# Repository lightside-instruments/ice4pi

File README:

hat4pi is an open hardware template for
development Raspberry Pi Hats published by Lightside Instruments AS.

The initial release hat4pi-1.0 includes schematic and PCB
design files for KiCAD.

The project is published by Lightside Instruments AS
under TAPR Open Hardware License. Read the LICENSE file
for details.

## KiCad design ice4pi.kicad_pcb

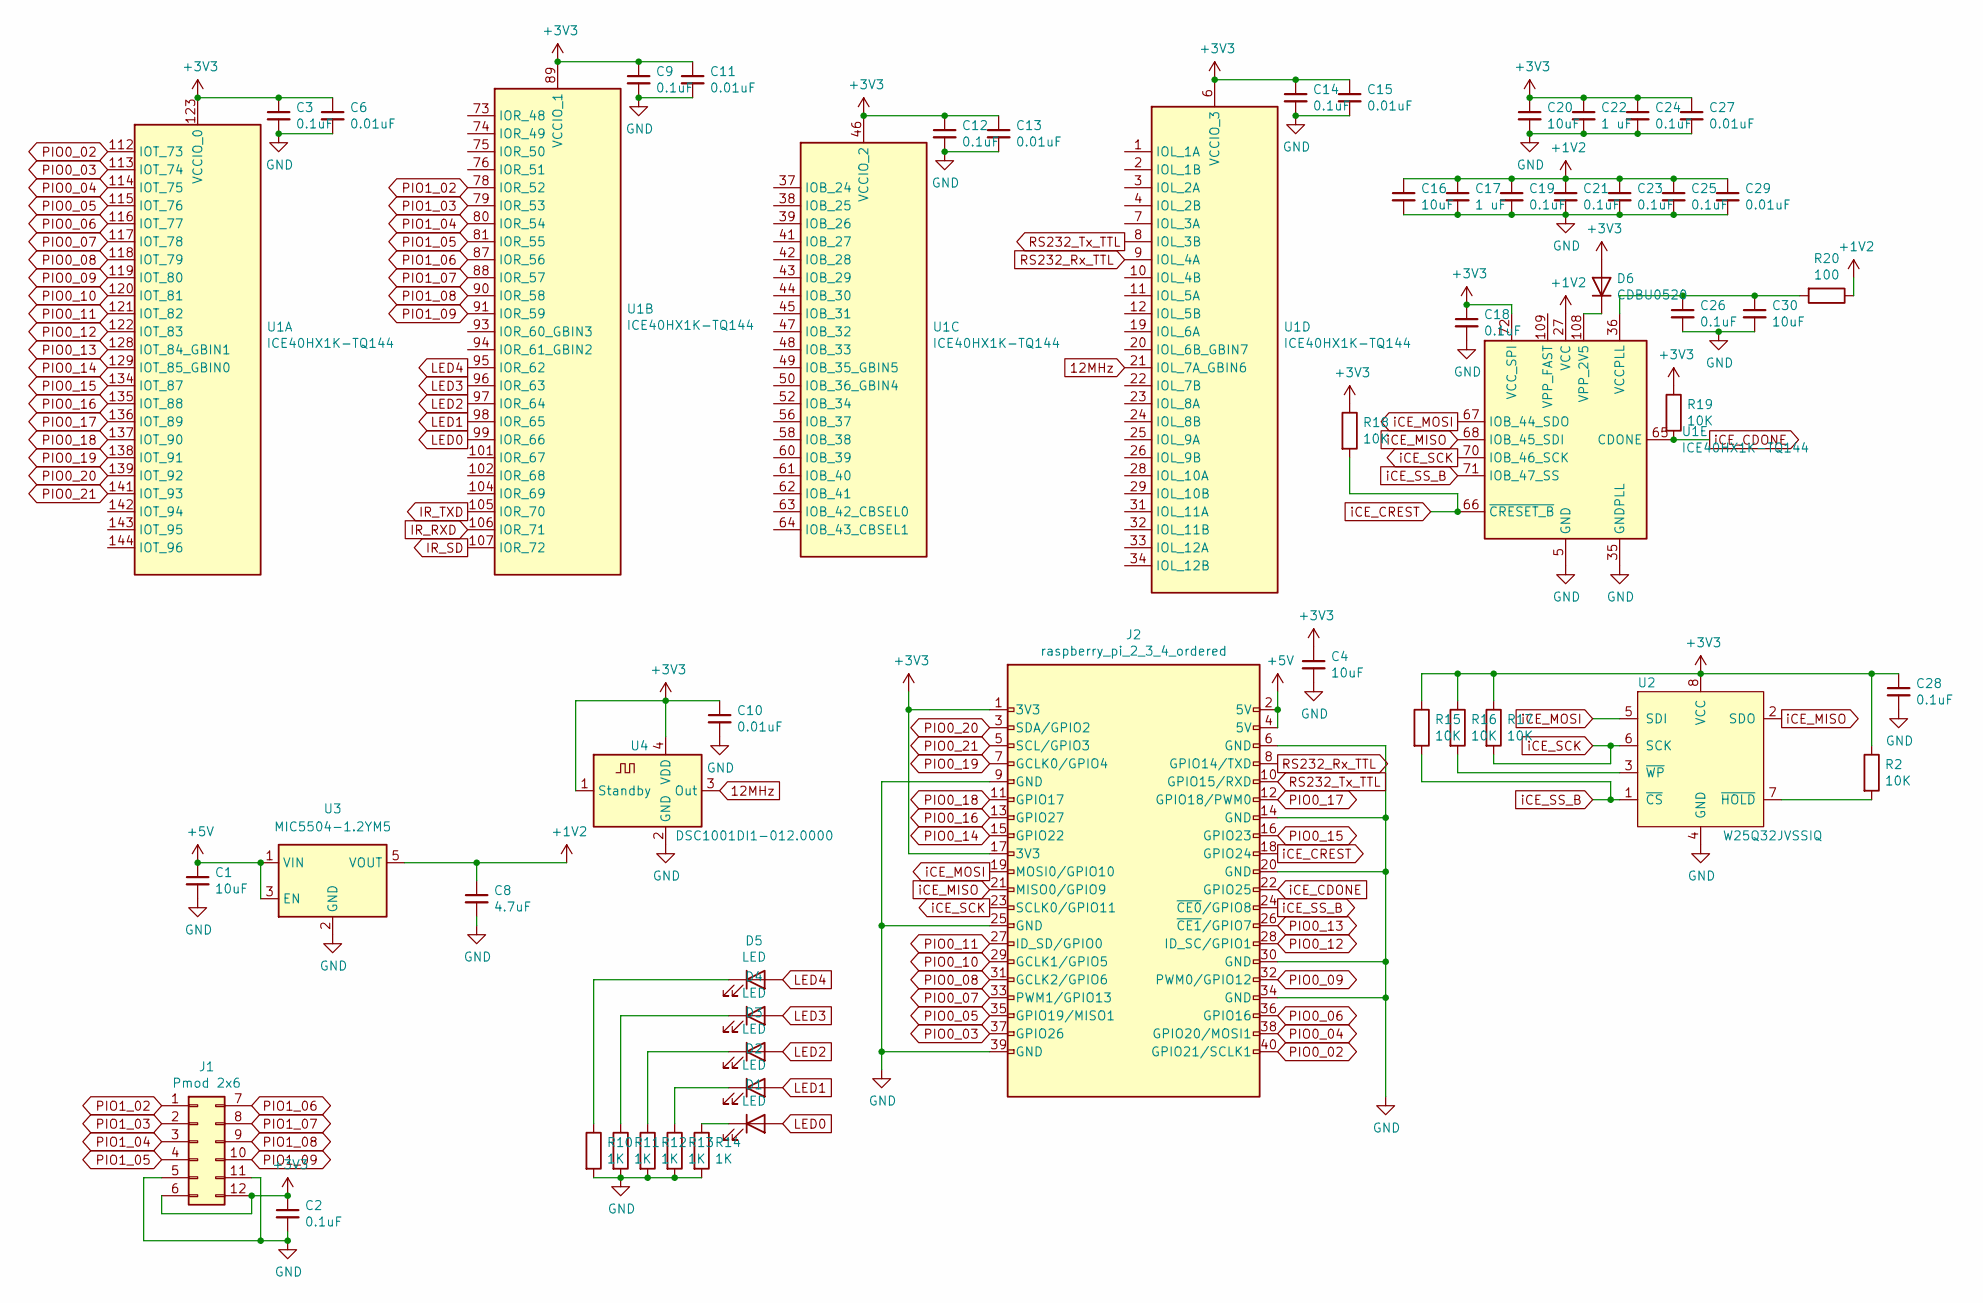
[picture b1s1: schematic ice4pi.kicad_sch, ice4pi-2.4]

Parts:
C1, C4, C16, C20, C30: 10uF; C_0402_1005Metric
C2, C3, C9, C12, C14, C18, C19, C21, C23, C24, C25, C26, C28: 0.1uF; C_0402_1005Metric
C6, C10, C11, C13, C15, C27, C29: 0.01uF; C_0402_1005Metric
C8: 4.7uF; C_0402_1005Metric
C17, C22: 1 uF; C_0402_1005Metric
D1, D2, D3, D4, D5: LED; LED_0402_1005Metric
D6: CDBU0520; D_0603_1608Metric
J1: Pmod 2x6; PinSocket_2x06_P2.54mm_Vertical_1to6_7to12
J2: raspberry_pi_2_3_4_ordered; PinSocket_2x20_P2.54mm_Vertical_1_04mm
R2, R15, R16, R17, R18, R19: 10K; R_0402_1005Metric
R10, R11, R12, R13, R14: 1K; R_0402_1005Metric
R20: 100; R_0402_1005Metric
U1: ICE40HX1K-TQ144; TQFP-144_20x20mm_P0.5mm
U2: W25Q32JVSSIQ; SOIC-8_3.9x4.9mm_P1.27mm
U3: MIC5504-1.2YM5; SOT-23-5
U4: DSC1001DI1-012.0000; Oscillator_SMD_Abracon_ASDMB-4Pin_2.5x2.0mm

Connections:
12MHz: U1.21 (IOL_7A_GBIN6), U4.3 (Out)
+1V2: C8.1, C16.1, C17.1, C19.1, C21.1, C23.1, C25.1, C29.1, R20.1, U1.27 (VCC), U1.51 (VCC), U1.92 (VCC), U1.111 (VCC), U3.5 (VOUT)
+3V3: C2.1, C3.1, C4.1, C6.1, C9.1, C10.1, C11.1, C12.1, C13.1, C14.1, C15.1, C18.1, C20.1, C22.1, C24.1, C27.1, C28.1, D6.2 (A), J1.6, J1.12, J2.1 (3V3), J2.17 (3V3), R2.1, R15.1, R16.1, R17.1, R18.1, R19.1, U1.6 (VCCIO_3), U1.30 (VCCIO_3), U1.46 (VCCIO_2), U1.57 (VCCIO_2), U1.72 (VCC_SPI), U1.89 (VCCIO_1), U1.100 (VCCIO_1), U1.123 (VCCIO_0), U1.133 (VCCIO_0), U2.8 (VCC), U4.1 (Standby), U4.4 (VDD)
+5V: C1.1, J2.2 (5V), J2.4 (5V), U3.1 (VIN), U3.3 (EN)
GND: C1.2, C2.2, C3.2, C4.2, C6.2, C8.2, C9.2, C10.2, C11.2, C12.2, C13.2, C14.2, C15.2, C16.2, C17.2, C18.2, C19.2, C20.2, C21.2, C22.2, C23.2, C24.2, C25.2, C26.2, C27.2, C28.2, C29.2, C30.2, J1.5, J1.11, J2.6 (GND), J2.9 (GND), J2.14 (GND), J2.20 (GND), J2.25 (GND), J2.30 (GND), J2.34 (GND), J2.39 (GND), R10.2, R11.2, R12.2, R13.2, R14.2, U1.5 (GND), U1.13 (GND), U1.14 (GND), U1.35 (GNDPLL), U1.59 (GND), U1.69 (GND), U1.86 (GND), U1.103 (GND), U1.132 (GND), U1.140 (GND), U2.4 (GND), U3.2 (GND), U4.2 (GND)
IR_RXD: U1.106 (IOR_71)
IR_SD: U1.107 (IOR_72)
IR_TXD: U1.105 (IOR_70)
LED0: D1.2 (A), U1.99 (IOR_66)
LED1: D2.2 (A), U1.98 (IOR_65)
LED2: D3.2 (A), U1.97 (IOR_64)
LED3: D4.2 (A), U1.96 (IOR_63)
LED4: D5.2 (A), U1.95 (IOR_62)
unnamed: C26.1, C30.1, R20.2, U1.36 (VCCPLL)
unnamed: D1.1 (K), R14.1
unnamed: D2.1 (K), R13.1
unnamed: D3.1 (K), R12.1
unnamed: D4.1 (K), R11.1
unnamed: D5.1 (K), R10.1
unnamed: D6.1 (K), U1.108 (VPP_2V5)
unnamed: R2.2, U2.7 (~HOLD)
unnamed: R16.2, U2.3 (~WP)
PIO0_02: J2.40 (GPIO21/SCLK1), U1.112 (IOT_73)
PIO0_03: J2.37 (GPIO26), U1.113 (IOT_74)
PIO0_04: J2.38 (GPIO20/MOSI1), U1.114 (IOT_75)
PIO0_05: J2.35 (GPIO19/MISO1), U1.115 (IOT_76)
PIO0_06: J2.36 (GPIO16), U1.116 (IOT_77)
PIO0_07: J2.33 (PWM1/GPIO13), U1.117 (IOT_78)
PIO0_08: J2.31 (GCLK2/GPIO6), U1.118 (IOT_79)
PIO0_09: J2.32 (PWM0/GPIO12), U1.119 (IOT_80)
PIO0_10: J2.29 (GCLK1/GPIO5), U1.120 (IOT_81)
PIO0_11: J2.27 (ID_SD/GPIO0), U1.121 (IOT_82)
PIO0_12: J2.28 (ID_SC/GPIO1), U1.122 (IOT_83)
PIO0_13: J2.26 (~CE1/GPIO7), U1.128 (IOT_84_GBIN1)
PIO0_14: J2.15 (GPIO22), U1.129 (IOT_85_GBIN0)
PIO0_15: J2.16 (GPIO23), U1.134 (IOT_87)
PIO0_16: J2.13 (GPIO27), U1.135 (IOT_88)
PIO0_17: J2.12 (GPIO18/PWM0), U1.136 (IOT_89)
PIO0_18: J2.11 (GPIO17), U1.137 (IOT_90)
PIO0_19: J2.7 (GCLK0/GPIO4), U1.138 (IOT_91)
PIO0_20: J2.3 (SDA/GPIO2), U1.139 (IOT_92)
PIO0_21: J2.5 (SCL/GPIO3), U1.141 (IOT_93)
PIO1_02: J1.1, U1.78 (IOR_52)
PIO1_03: J1.2, U1.79 (IOR_53)
PIO1_04: J1.3, U1.80 (IOR_54)
PIO1_05: J1.4, U1.81 (IOR_55)
PIO1_06: J1.7, U1.87 (IOR_56)
PIO1_07: J1.8, U1.88 (IOR_57)
PIO1_08: J1.9, U1.90 (IOR_58)
PIO1_09: J1.10, U1.91 (IOR_59)
RS232_Rx_TTL: J2.8 (GPIO14/TXD), U1.9 (IOL_4A)
RS232_Tx_TTL: J2.10 (GPIO15/RXD), U1.8 (IOL_3B)
iCE_CDONE: J2.22 (GPIO25), R19.2, U1.65 (CDONE)
iCE_CREST: J2.18 (GPIO24), R18.2, U1.66 (~CRESET_B)
iCE_MISO: J2.21 (MISO0/GPIO9), U1.68 (IOB_45_SDI), U2.2 (SDO)
iCE_MOSI: J2.19 (MOSI0/GPIO10), U1.67 (IOB_44_SDO), U2.5 (SDI)
iCE_SCK: J2.23 (SCLK0/GPIO11), R17.2, U1.70 (IOB_46_SCK), U2.6 (SCK)
iCE_SS_B: J2.24 (~CE0/GPIO8), R15.2, U1.71 (IOB_47_SS), U2.1 (~CS)

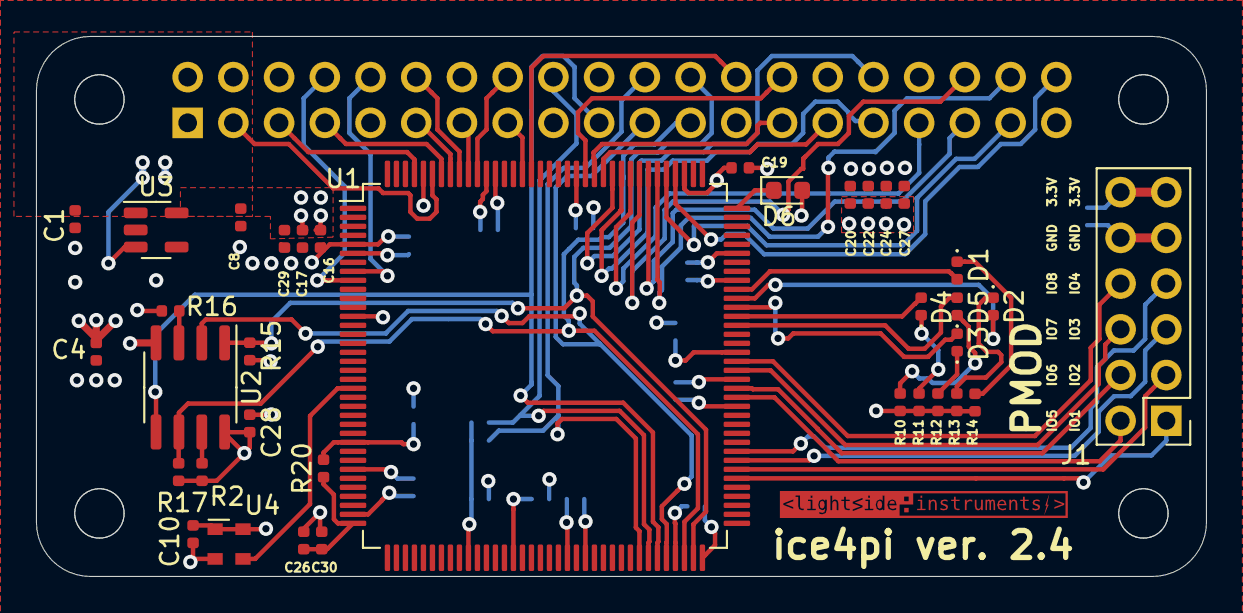
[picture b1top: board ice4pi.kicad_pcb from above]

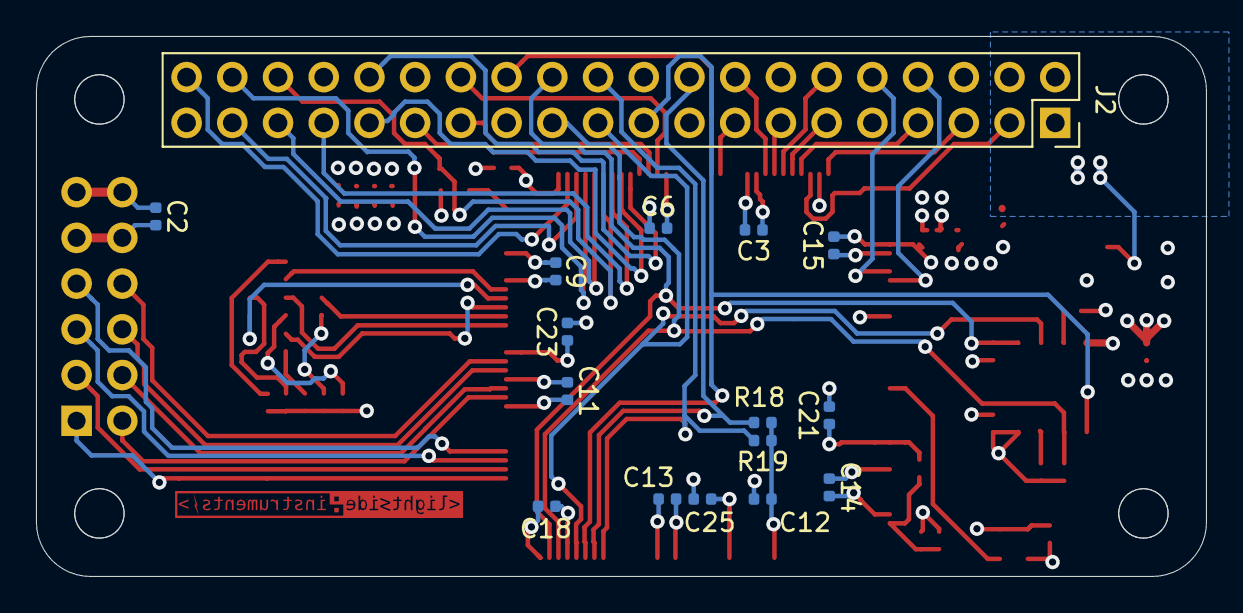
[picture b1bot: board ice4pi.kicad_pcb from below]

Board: 4 copper layers, 65.0 x 30.0 mm, 53 parts (16 on the bottom side), 55 nets.

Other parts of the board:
svg2mod: G***; lsi-logo-16mm-fcu

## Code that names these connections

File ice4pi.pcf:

# 5 LEDs  (identical to iCE40HX-1K iCEstick)
set_io D1 99
set_io D2 98
set_io D3 97
set_io D4 96
set_io D5 95

# 12MHz clock (identical to iCE40HX-1K iCEstick)
set_io clk 21

# pmod IO
set_io P1 78
set_io P2 79
set_io P3 80
set_io P4 81
set_io P5 87
set_io P6 88
set_io P7 90
set_io P8 91


#ice4pi Raspberry Pi 40-pin connector
#      R1  3V3
set_io R3  139
set_io R5  141
set_io R7  138
#      R9  GND
set_io R11 137
set_io R13 135
set_io R15 129
#      R17 3V3
set_io R19 67 #iCE_MOSI

set_io R21 68 #iCE_MISO
set_io R23 70 #iCE_SCK
#      R25 GND
set_io R27 121
set_io R29 120
set_io R31 118
set_io R33 117
set_io R35 115
set_io R37 113
#      R39 GND

#      R2   5V
#      R4   5V
#      R6  GND
set_io R8    9 # RS232_Rx_TTL
set_io R10   8 # RS232_Tx_TTL
set_io R12 136
#      R14 GND
set_io R16 134
set_io R18  66 # iCE_CREST

#      R20 GND
set_io R22  65 # iCE_DONE 
set_io R24  71 # iCE_SS_B
set_io R26 128
set_io R28 122
#      R30 GND
set_io R32 119
#      R34 GND
set_io R36 116
set_io R38 114
set_io R40 112

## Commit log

2021-01-31 Release ice4pi-spark-6x-sfp-1.2.1
2021-07-06 Release ice4ultra96-1.2-1
2021-07-06 Release ice4ultra96-1.2-2
2021-09-08 Release gpsclock4ultra96-1.0-1
2021-09-08 Release clockinput4ultra96-1.0-1
2022-02-08 Release ice4pi-2.0
2023-01-08 Release ice4pi-2.1
2023-01-08 Release ice4pi-2.2
2023-01-17 Changed example to use flashrom from APT repository.
    The package from Debian Bullseye seem to work fine, no need to
    build your own version.
2023-01-17 Adjusted example readme to mention 'make load' need root access.
    Without root access, the script report these errors:
    ./ice4pi_prog: line 3: /sys/class/gpio/gpio24/direction: Permission denied
    ./ice4pi_prog: line 4: /sys/class/gpio/gpio24/value: Permission denied
    ./ice4pi_prog: line 6: echo: write error: Operation not permitted
    Besides these messages, the flashing seem to be successful.
2023-01-22 Release ice4pi-2.3
2023-02-08 Release ice4ultra96-1.2-3
2023-02-08 Release ice4pi-spark-6x-sfp-1.2.1-1
2023-02-16 Release ice4pi-2.4
2023-04-21 Release etherenet4pizero-1.0
2023-04-25 Release ethernet4pizero-direct-spi-1.0
2023-05-27 Release ice4pi-gpib-2.4
2023-10-04 Release clockinput4ultra96-1.1
2023-10-07 Release gpsclock4ultra96-1.1
2024-03-06 Release ice4pi-2.4.1
2024-05-07 Release ice4pi-2.4.2
2024-07-21 Release ice4pi-spark-6x-sfp-1.2.1-2
2025-01-20 Release ice4pi-2.4.3
2025-01-20 Release ice4pi-signal-integrity-2.4.3-1
2025-03-22 example/Makefile: replace arachne-pnr with nextpnr
2025-03-22 example/README: document dependency on nextpnr-ice40 package
2025-07-16 Explain in the example README what the example is doing.
    Fixes #3
2025-07-16 Let make track build dependencies in a fine grained approach.
    This also ensure failed build do not replace existing files.
2026-02-25 Release ice4pi-2.4.4
2026-02-25 Release ice4pi-2.4.5
2026-06-02 Release ice4pi-2.4.6
2026-06-03 Release hat4pi-1.0
